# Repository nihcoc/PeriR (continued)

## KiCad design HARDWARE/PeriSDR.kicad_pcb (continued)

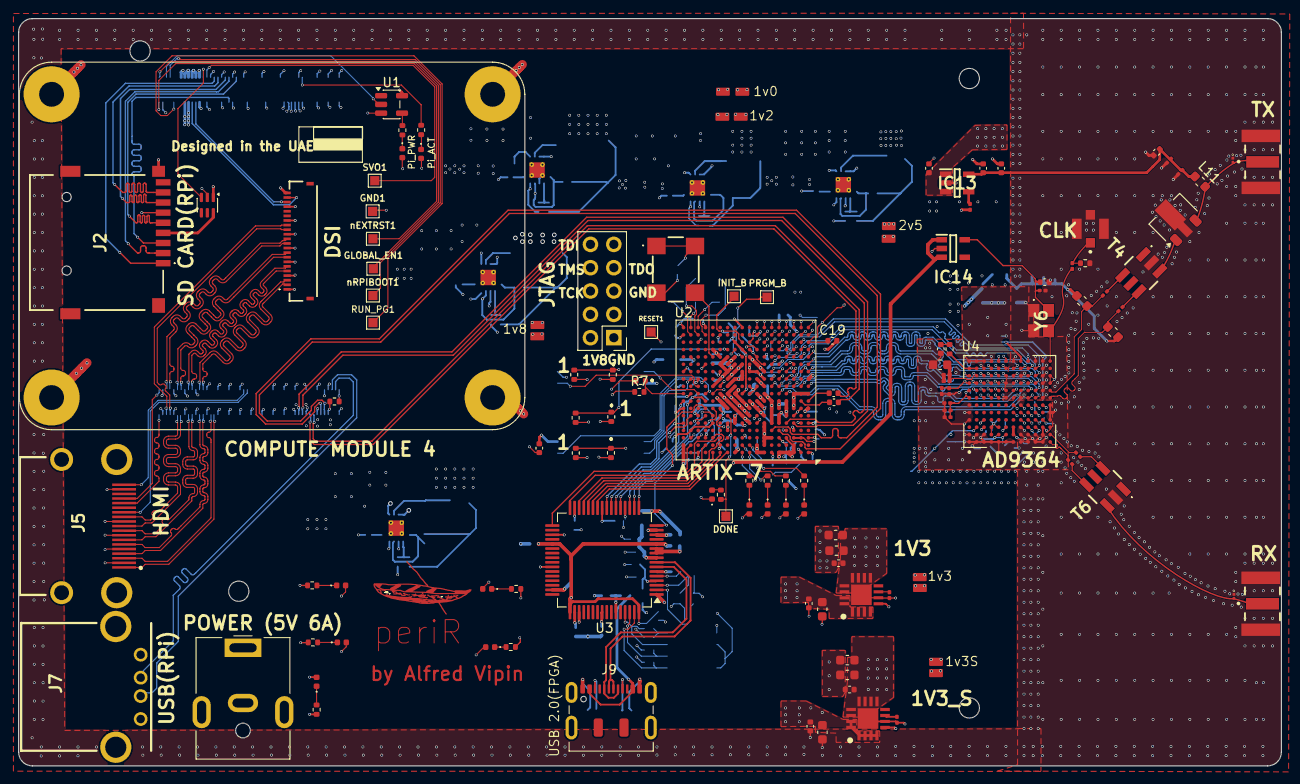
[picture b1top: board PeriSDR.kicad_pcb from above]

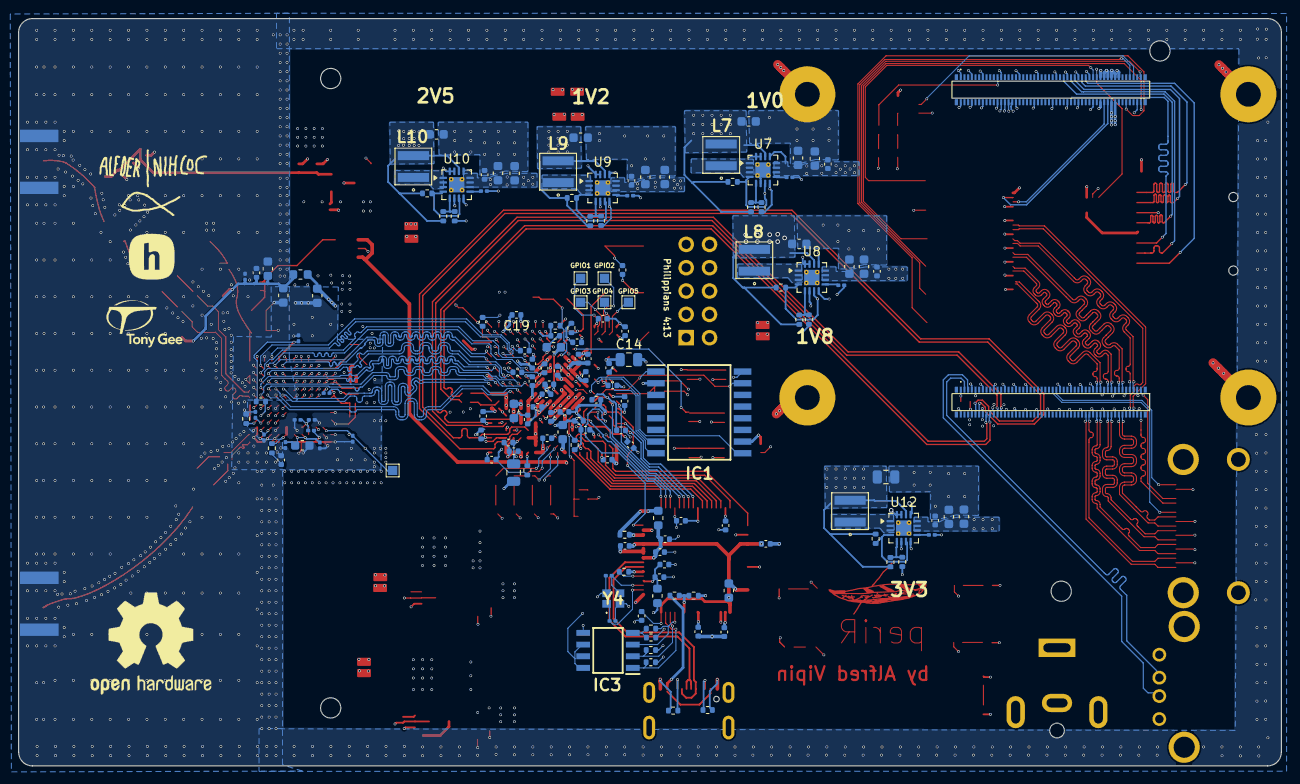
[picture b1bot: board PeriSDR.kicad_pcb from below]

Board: 6 copper layers, 137.4 x 81.3 mm, 266 parts (152 on the bottom side), 228 nets.

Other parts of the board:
C19#2: 4.7uF; C_0402_1005Metric

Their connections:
+2V5: C19#2.1; also elsewhere on the board
GND: C19#2.2; also elsewhere on the board

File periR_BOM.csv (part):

Index,LCSC#,MPN,Manufacturer,Package,Board Ref,Description,,Quantity,MOQ,Unit Price($),Extended Price($),Product Link
1,C444946,AD9364BBCZ,ADI,BGA-144,U4,-122dBm 70MHz~6GHz 1.2V~3.3V BGA-144 RF Transceiver ICs RoHS,,1,1,96.5166,96.52,https://www.lcsc.com/product-detail/C444946.html
2,C5199907,SMA-J-P-H-ST-EM1,Samtec,SMD,"J12,J13,J14",Connector Receptacle SMA 50Ω,,3,1,4.8959,14.69,https://www.lcsc.com/product-detail/C5199907.html
3,C337502,TPS62130ARGTR,TI,QFN-16-EP(3x3),"U7,U8,U9,U10,U12",2.5MHz Step-down type Adjustable 900mV~6V 3A QFN-16-EP(3x3) Voltage Regulators - DC DC Switching Regulators RoHS,,5,1,0.791,3.96,https://www.lcsc.com/product-detail/C337502.html
4,C9002,X322512MSB4SI,YXC Crystal Oscillators,SMD3225-4P,Y4,Crystal 12MHz ±10ppm 20pF SMD3225-4P,,5,5,0.1012,0.51,https://www.lcsc.com/product-detail/C9002.html
5,C55061480,PUBFA-R23A-003,YUWENFA,Through Hole,J7,"USB 2.0 Through Hole USB, DVI, HDMI Connector Adapters RoHS",,5,5,0.0583,0.29,https://www.lcsc.com/product-detail/C55061480.html
6,C720616,HDMI-001S,XUNPU,SMD,J5,"HDMI-A Receptacle Connector 19 Position Surface Mount, Right Angle",,5,5,0.2424,1.21,https://www.lcsc.com/product-detail/C720616.html
7,C2765186,TYPE-C 16PIN 2MD(073),SHOU HAN,SMD,J9,"USB-C (USB TYPE-C) Receptacle Connector 16 Position Surface Mount, Right Angle",,20,20,0.0707,1.41,https://www.lcsc.com/product-detail/C2765186.html
8,C7529389,TF-CARD H1.8,SHOU HAN,SMD,J2,Micro SD card (TF card) Connector and Ejector Push-Push Surface Mount,,10,10,0.0608,0.61,https://www.lcsc.com/product-detail/C7529389.html
9,C720557,DC-005-A200,XUNPU,Through Hole,J10,"Power Barrel Connector Jack 2mm ID 6.4mm OD Through Hole, Right Angle",,5,5,0.1294,0.65,https://www.lcsc.com/product-detail/C720557.html
10,C502010,MLJ1608WR33JT000,TDK,603,"L13,L14",500mA 330nH ±5% 320mΩ 650mA Multilayer inductor 0603 Fixed Inductors RoHS,,10,10,0.0744,0.74,https://www.lcsc.com/product-detail/C502010.html
11,C85837,BLM21AG601SN1D,muRata,805,FB4,600Ω@100MHz 1 Line Ferrite Bead 0805 700mA 210mΩ,,20,20,0.0618,1.24,https://www.lcsc.com/product-detail/C85837.html
12,C424649,DF40HC(3.0)-100DS-0.4V(51),HRS,"SMD,P=0.4mm",H1,nan,,2,1,1.8918,3.78,https://www.lcsc.com/product-detail/C424649.html
13,C25120,0402WGF499JTCE,UNI-ROYAL,402,R33,49.9Ω ±1% 62.5mW 0402 Thick Film Resistor,,100,100,0.0011,0.11,https://www.lcsc.com/product-detail/C25120.html
14,C2906901,FRC0402J1R0 TS,FOJAN,402,"R31,R32",1Ω ±5% 62.5mW 0402 Thick Film Resistor,,100,100,0.0016,0.16,https://www.lcsc.com/product-detail/C2906901.html
15,C852856,RT0402BRD075K1L,YAGEO,402,"R27,R28",5.1kΩ 62.5mW 50V Thin Film Resistor ±25ppm/℃ ±0.1% 0402 Chip Resistor - Surface Mount RoHS,,50,50,0.0216,1.08,https://www.lcsc.com/product-detail/C852856.html
16,C2909316,FRC0402F1202TS,FOJAN,402,R25,12kΩ ±1% 62.5mW 0402 Thick Film Resistor,,100,100,0.0014,0.14,https://www.lcsc.com/product-detail/C2909316.html
17,C190095,RT0402BRD0710KL,YAGEO,402,"R19,R20,R24,R30,R35",62.5mW 10kΩ 50V Thin Film Resistor ±25ppm/℃ ±0.1% 0402 Chip Resistor - Surface Mount RoHS,,50,50,0.0207,1.04,https://www.lcsc.com/product-detail/C190095.html
18,C2906865,FRC0402F2201TS,FOJAN,402,"R17,R18",2.2kΩ ±1% 62.5mW 0402 Thick Film Resistor,,100,100,0.0016,0.16,https://www.lcsc.com/product-detail/C2906865.html
19,C106232,RC0402FR-07100RL,YAGEO,402,R8,100Ω 62.5mW 50V Thick Film Resistor ±100ppm/℃ ±1% 0402 Chip Resistor - Surface Mount RoHS,,100,100,0.0013,0.13,https://www.lcsc.com/product-detail/C106232.html
20,C242160,ERJ2GE0R00X,PANASONIC,402,R7,100mW 0Ω Thick Film Resistor -100ppm/℃~+600ppm/℃ 0402 Chip Resistor - Surface Mount RoHS,,100,100,0.0047,0.47,https://www.lcsc.com/product-detail/C242160.html
21,C71626,CRCW0402330RFKED,VISHAY,402,R5,63mW 330Ω Thick Film Resistor ±100ppm/℃ ±1% 0402 Chip Resistor - Surface Mount RoHS,,100,100,0.0037,0.37,https://www.lcsc.com/product-detail/C71626.html
22,C1884625,MCS04020C4701FE000,VISHAY,402,"R2,R3,R29",100mW 4.7kΩ 50V Thin Film Resistor ±50ppm/℃ ±1% 0402 Chip Resistor - Surface Mount RoHS,,20,20,0.0304,0.61,https://www.lcsc.com/product-detail/C1884625.html
23,C852624,RT0402BRD071KL,YAGEO,402,"R1,R2(DNP)1,R3(DNP)1,R4,R5(DNP)1,R6,R26",1kΩ 62.5mW 50V Thin Film Resistor ±25ppm/℃ ±0.1% 0402 Chip Resistor - Surface Mount RoHS,,50,50,0.0199,1,https://www.lcsc.com/product-detail/C852624.html
24,C5633358,ECS-TXO-32CSMV-400-BN-TR,ECS,SMD3225-4P,Y6,40MHz SMD3225-4P Oscillators RoHS,,1,1,2.6285,2.63,https://www.lcsc.com/product-detail/C5633358.html
25,C7522691,LQW18AS43NJ00D,muRata,603,L11,600mA 43nH ±5% 280mΩ Wire-wound chip inductor 0603 Fixed Inductors RoHS,,5,5,0.0895,0.45,https://www.lcsc.com/product-detail/C7522691.html
26,C51048295,FRC0402F1432TS,FOJAN,402,R34,62.5mW 14.3kΩ 50V Thick Film Resistor ±1% 0402 Chip Resistor - Surface Mount RoHS,,100,100,0.0008,0.08,https://www.lcsc.com/product-detail/C51048295.html
27,C2906952,FRC0402J513 TS,FOJAN,402,R84,51kΩ ±5% 62.5mW 0402 Thick Film Resistor,,100,100,0.0013,0.13,https://www.lcsc.com/product-detail/C2906952.html
28,C144785,AC0402FR-07200KL,YAGEO,402,"R85,R125",62.5mW 200kΩ 50V Thick Film Resistor ±100ppm/℃ ±1% 0402 Chip Resistor - Surface Mount RoHS,,100,100,0.0018,0.18,https://www.lcsc.com/product-detail/C144785.html
29,C481918,CRCW0402100KFKED,VISHAY,402,"R86,R87,R88,R89,R91,R127,R129,R133",100kΩ 63mW 50V Thick Film Resistor ±1% ±100ppm/℃ 0402 Chip Resistor - Surface Mount RoHS,,100,100,0.0038,0.38,https://www.lcsc.com/product-detail/C481918.html
30,C7467320,FRC0402J164 TS,FOJAN,402,R126,62.5mW 160kΩ 50V Thick Film Resistor ±5% ±100ppm/℃ 0402 Chip Resistor - Surface Mount RoHS,,100,100,0.0011,0.11,https://www.lcsc.com/product-detail/C7467320.html
31,C2906873,FRC0402F4992TS,FOJAN,402,R128,49.9kΩ ±1% 62.5mW 0402 Thick Film Resistor,,100,100,0.0015,0.15,https://www.lcsc.com/product-detail/C2906873.html
32,C2515044,RN73H1ETTP2133D25,KOA,402,R130,62.5mW 213kΩ Metal Film Resistor ±0.5% ±25ppm/℃ 0402 Chip Resistor - Surface Mount RoHS,,1,1,0.0568,0.06,https://www.lcsc.com/product-detail/C2515044.html
33,C4180598,RE0402BRE07309KL,YAGEO,402,R134,309kΩ 62.5mW Thick Film Resistor ±50ppm/℃ ±0.1% 0402 Chip Resistor - Surface Mount RoHS,,20,20,0.0111,0.22,https://www.lcsc.com/product-detail/C4180598.html
34,C494678,TCM1-63AX+,Mini-Circuits,SMD-6P,"T4,T6",9.42dB 8° 10MHz~6GHz 2.5dB 50Ω:50Ω SMD-6P Balun RoHS,,2,1,17.6099,35.22,https://www.lcsc.com/product-detail/C494678.html
35,C1521759,XC7A50T-2CSG325I,AMD/XILINX,FPGA-325(15x15),U2,52160 FPGA-325(15x15) FPGAs (Field Programmable Gate Array) RoHS,,1,1,52.4575,52.46,https://www.lcsc.com/product-detail/C1521759.html
36,C27882,FT2232HL-REEL,FTDI,LQFP-64(10x10),U3,480Mbps USB 2.0 LQFP-64(10x10) Interface Controllers RoHS,,1,1,12.4162,12.42,https://www.lcsc.com/product-detail/C27882.html
37,C3193264,PGA-102+,Mini-Circuits,SOT-89,U11,10.4dB 50MHz~6GHz 3.1V~3.5V 3.9dB 17.5dBm 83mA SOT-89 RF Amplifiers RoHS,,1,1,2.3356,2.34,https://www.lcsc.com/product-detail/C3193264.html
38,C1997058,SG-8018CA 100.0000M-TJHSA0,EPSON,SMD7050-4P,Y2,100MHz SMD7050-4P Oscillators RoHS,,1,1,1.0742,1.07,https://www.lcsc.com/product-detail/C1997058.html
39,C76941,GRM033R71A103KA01D,muRata,201,"C284,C292,C305",10nF ±10% 10V Ceramic Capacitor X7R 0201,,100,100,0.005,0.5,https://www.lcsc.com/product-detail/C76941.html
40,C368809,CL05A475KP5NRNC,Samsung Electro-Mechanics,402,"C1,C2,C9,C12,C13,C18,C19,C24,C25,C30,C31,C46,C85,C86,C313",4.7uF ±10% 10V Ceramic Capacitor X5R 0402,,50,50,0.0116,0.58,https://www.lcsc.com/product-detail/C368809.html
41,C6663208,298W107X0004M2T,VISHAY,603,"C3,C14",100uF ±20% 4V Tantalum Capacitors 0603,,2,1,1.8719,3.74,https://www.lcsc.com/product-detail/C6663208.html
42,C92361,CL05A474KA5NNNC,Samsung Electro-Mechanics,402,"C4,C5,C6,C11,C15,C16,C17,C20,C21,C22,C23,C26,C27,C28,C29,C32,C33,C34,C35",470nF ±10% 25V Ceramic Capacitor X5R 0402,,20,10,0.0163,0.33,https://www.lcsc.com/product-detail/C92361.html
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
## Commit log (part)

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2026-06-22 Enhance README with project details and specifications
    Expanded the README to include detailed project specifications, hardware design, and software information.
2026-06-22 Update README with image and Fallout Zine header
    Added an image and updated the section header for Fallout Zine.
2026-06-22 Add special thanks to Hack Club and Fallout 2026
    Added special thanks section to the README.
2026-06-22 Fix formatting in FPGA Interfaces section
2026-06-22 Update README with sequencing management details
    Add information about sequencing management using EN and PG pins.
2026-06-22 Fix formatting in README.md table entries
2026-06-22 Update PCIe interface details in README
2026-06-23 Add image to Fallout Zine section
    Added a new image to the Fallout Zine section in README.
2026-06-23 Update image in Fallout Zine section
    Replaced an image in the Fallout Zine section of the README.
2026-06-23 Update README with Fallout Zine and Layers details
    Added sections for Fallout Zine and Layers with images.
2026-06-23 Add periR_BOM.csv file
2026-06-23 Add Bill of Materials section to README
    Added a Bill of Materials section with detailed component information including part numbers, manufacturers, quantities, and links.
2026-06-23 Add Bill of Materials section to README
2026-06-23 Add Compute Module 4 and PCB details to README
2026-06-23 Update total cost in Bill of Materials section
2026-06-23 Fix link for Compute Module 4 and add journal reference
    Updated the link for Compute Module 4 and added a journal link.
2026-06-27 Add project motivation section to README
    Added a section explaining the motivation behind the project and the challenges involved in creating a custom SDR.
2026-06-27 Refine RF transceiver details and update HDL reference
    Removed redundant details about the RF transceiver's signalling standard and clock specifications. Updated reference HDL link for clarity.
2026-06-27 Update total cost and change PCB to PCBA
